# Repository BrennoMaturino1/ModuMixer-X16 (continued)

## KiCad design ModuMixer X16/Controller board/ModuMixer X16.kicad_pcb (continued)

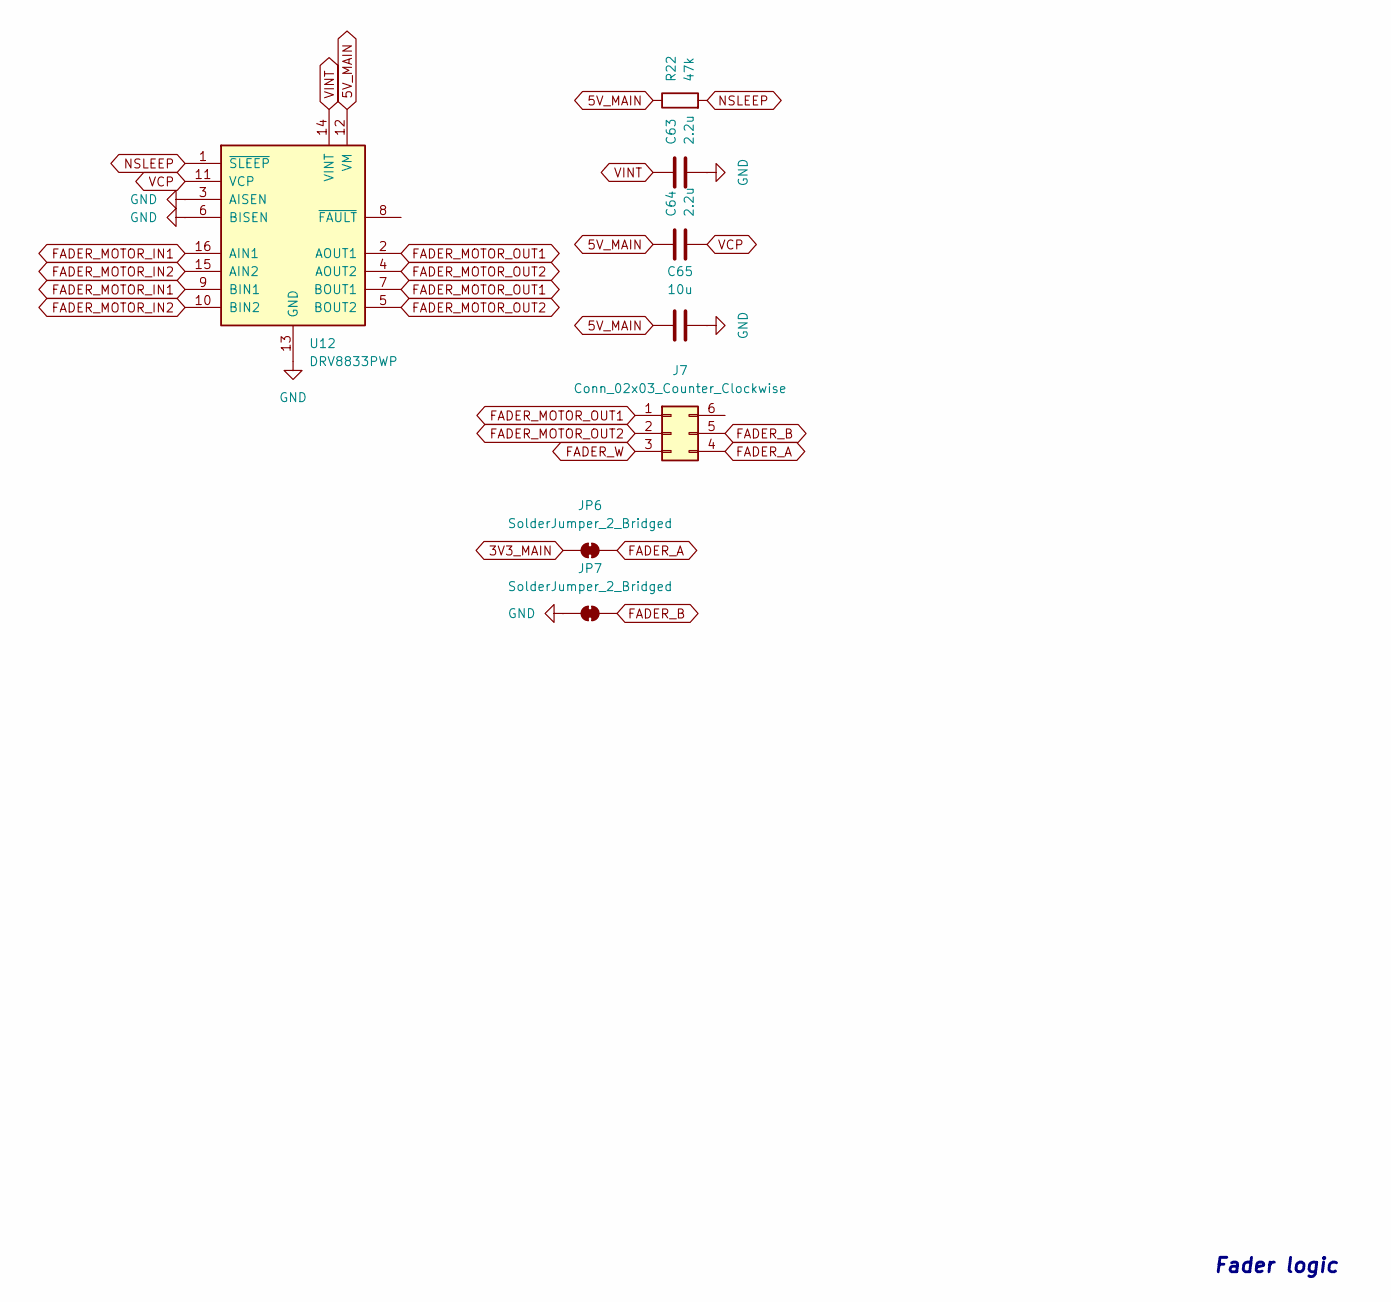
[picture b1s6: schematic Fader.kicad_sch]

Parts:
C63, C64: 2.2u; C_0603_1608Metric
C65: 10u; C_0603_1608Metric
J7: Conn_02x03_Counter_Clockwise; PinHeader_2x03_P2.54mm_Vertical
JP6, JP7: SolderJumper_2_Bridged; SolderJumper-2_P1.3mm_Bridged2Bar_Pad1.0x1.5mm
R22: 47k; R_0603_1608Metric
U12: DRV8833PWP; HTSSOP-16-1EP_4.4x5mm_P0.65mm_EP3.4x5mm_Mask2.46x2.31mm_The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

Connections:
3V3_MAIN: JP6.1 (A); also elsewhere on the board
5V_MAIN: C64.1, C65.1, R22.1, U12.12 (VM); also elsewhere on the board
FADER_A: J7.4, JP6.2 (B)
FADER_B: J7.5, JP7.2 (B)
FADER_MOTOR_IN1: U12.9 (BIN1), U12.16 (AIN1); also elsewhere on the board
FADER_MOTOR_IN2: U12.10 (BIN2), U12.15 (AIN2); also elsewhere on the board
FADER_MOTOR_OUT1: J7.1, U12.2 (AOUT1), U12.7 (BOUT1)
FADER_MOTOR_OUT2: J7.2, U12.4 (AOUT2), U12.5 (BOUT2)
FADER_W: J7.3; also elsewhere on the board
GND: C63.2, C65.2, JP7.1 (A), U12.3 (AISEN), U12.6 (BISEN), U12.13 (GND), U12.17 (GND); also elsewhere on the board
NSLEEP: R22.2, U12.1 (~SLEEP)
VCP: C64.2, U12.11 (VCP)
VINT: C63.1, U12.14 (VINT)

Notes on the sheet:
Fader logic

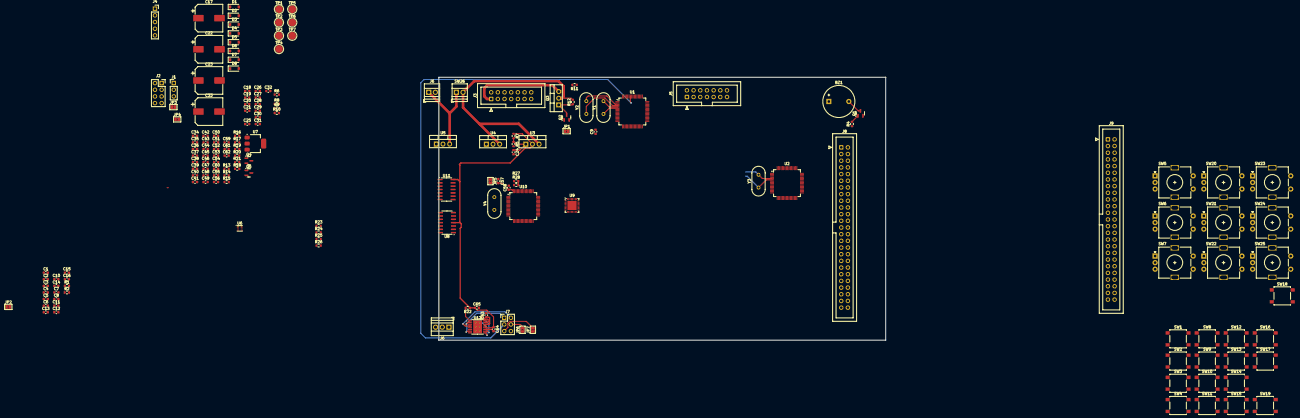
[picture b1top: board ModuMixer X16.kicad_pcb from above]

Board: 2 copper layers, 170.0 x 100.0 mm, 173 parts (1 on the bottom side), 137 nets.

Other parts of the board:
J6#2: Screw_Terminal_01x03; TerminalBlock_Xinya_XY308-2.54-3P_1x03_P2.54mm_Horizontal
TP3: 5V_MAIN; TestPoint_Pad_D3.0mm
TP4: 3V3_MAIN; TestPoint_Pad_D3.0mm
TP5: 3V3_STBY; TestPoint_Pad_D3.0mm
TP7: 3V3_ALW; TestPoint_Pad_D3.0mm

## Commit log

2024-07-31 Upload project files
2024-08-01 update idk
2024-08-01 idk testing github desktop
2024-08-01 Connected DSP to Main
    Connected SPI Data lines from main (master) MCU to DSP (slave) MCU
2024-08-01 Added input modules
2024-08-02 Starting work on output modules
    tomorrow i'll be making the output modules i guess
2024-08-11 Added schematics pdf
2024-08-24 Switching microcontrollers
    Midway through switching all microcontrollers in the project to STM32F103RC due to price constraints
2024-08-24 Midway through MCU change
2024-08-28 Midway through MCU replacement
    Sometimes i feel like it would be better to start over considering it's a digital mixer.
    The only thing left is doing the DSP connections and calculating the values for a 16mhz crystal on all 3 MCUs
2024-08-28 MCU replacement done
    I finally did everything (i guess), i replaced the MCUs, set the clock components, connected them, idk i guess it's ok now, we just gotta make that pcb
2024-08-29 asdasgashg
    sfjhadgdjasdg
2024-08-29 Changed all labels to global
    I made it in a rather hacky way (editing all files on notepad with Ctrl + H), i'm only reverting this if something breaks
2024-08-31 MCU replacement finished
